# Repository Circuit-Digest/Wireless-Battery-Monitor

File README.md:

# Wireless-Battery-Monitor

<br>

Batteries are everywhere and can be found in many of the day-to-day life equipment. Most of them are powered by Li ion or LIfepo4 batteries nowadays. Even though they need much less maintenance when compared to traditional Lead acid batteries, it is essential to regularly monitor them to avoid damage or even accidents. That’s where BMS comes into play. They not only provide safety but also help extend battery life. But the problem with most common BMSs is that, if we want to manually check the battery health, we will have to physically access it. There are BMS’s that offer wireless monitoring functionality, but the issue is that they are pretty expensive. That’s why we have decided to design and build a DIY wireless battery monitoring system, which can be used with the existing BMS.
For this project we have chosen the AD7280 Lithium-Ion Battery Monitoring chip from Analog Devices, and for wireless connectivity we have chosen our favourite ESP32. The AD7280 is capable of monitoring up to 6S battery configuration. Here we have configured it to monitor 4S battery configuration since that’s the most commonly used battery system. The AD7280 offers a 12bit ADC with a conversion time of 1 us per channel. It also features cell balancing function, which can be controlled manually. The ESP32 is used for communication and to host a Async webserver which can be used to monitor the cell voltages and charge levels.

<br>
[Note: As this projects are very simple we are only providing the code, schemaitic, and a few essential images if you want to get the images or code explanations do check out the Circuit Digest website.
<br>
<br>

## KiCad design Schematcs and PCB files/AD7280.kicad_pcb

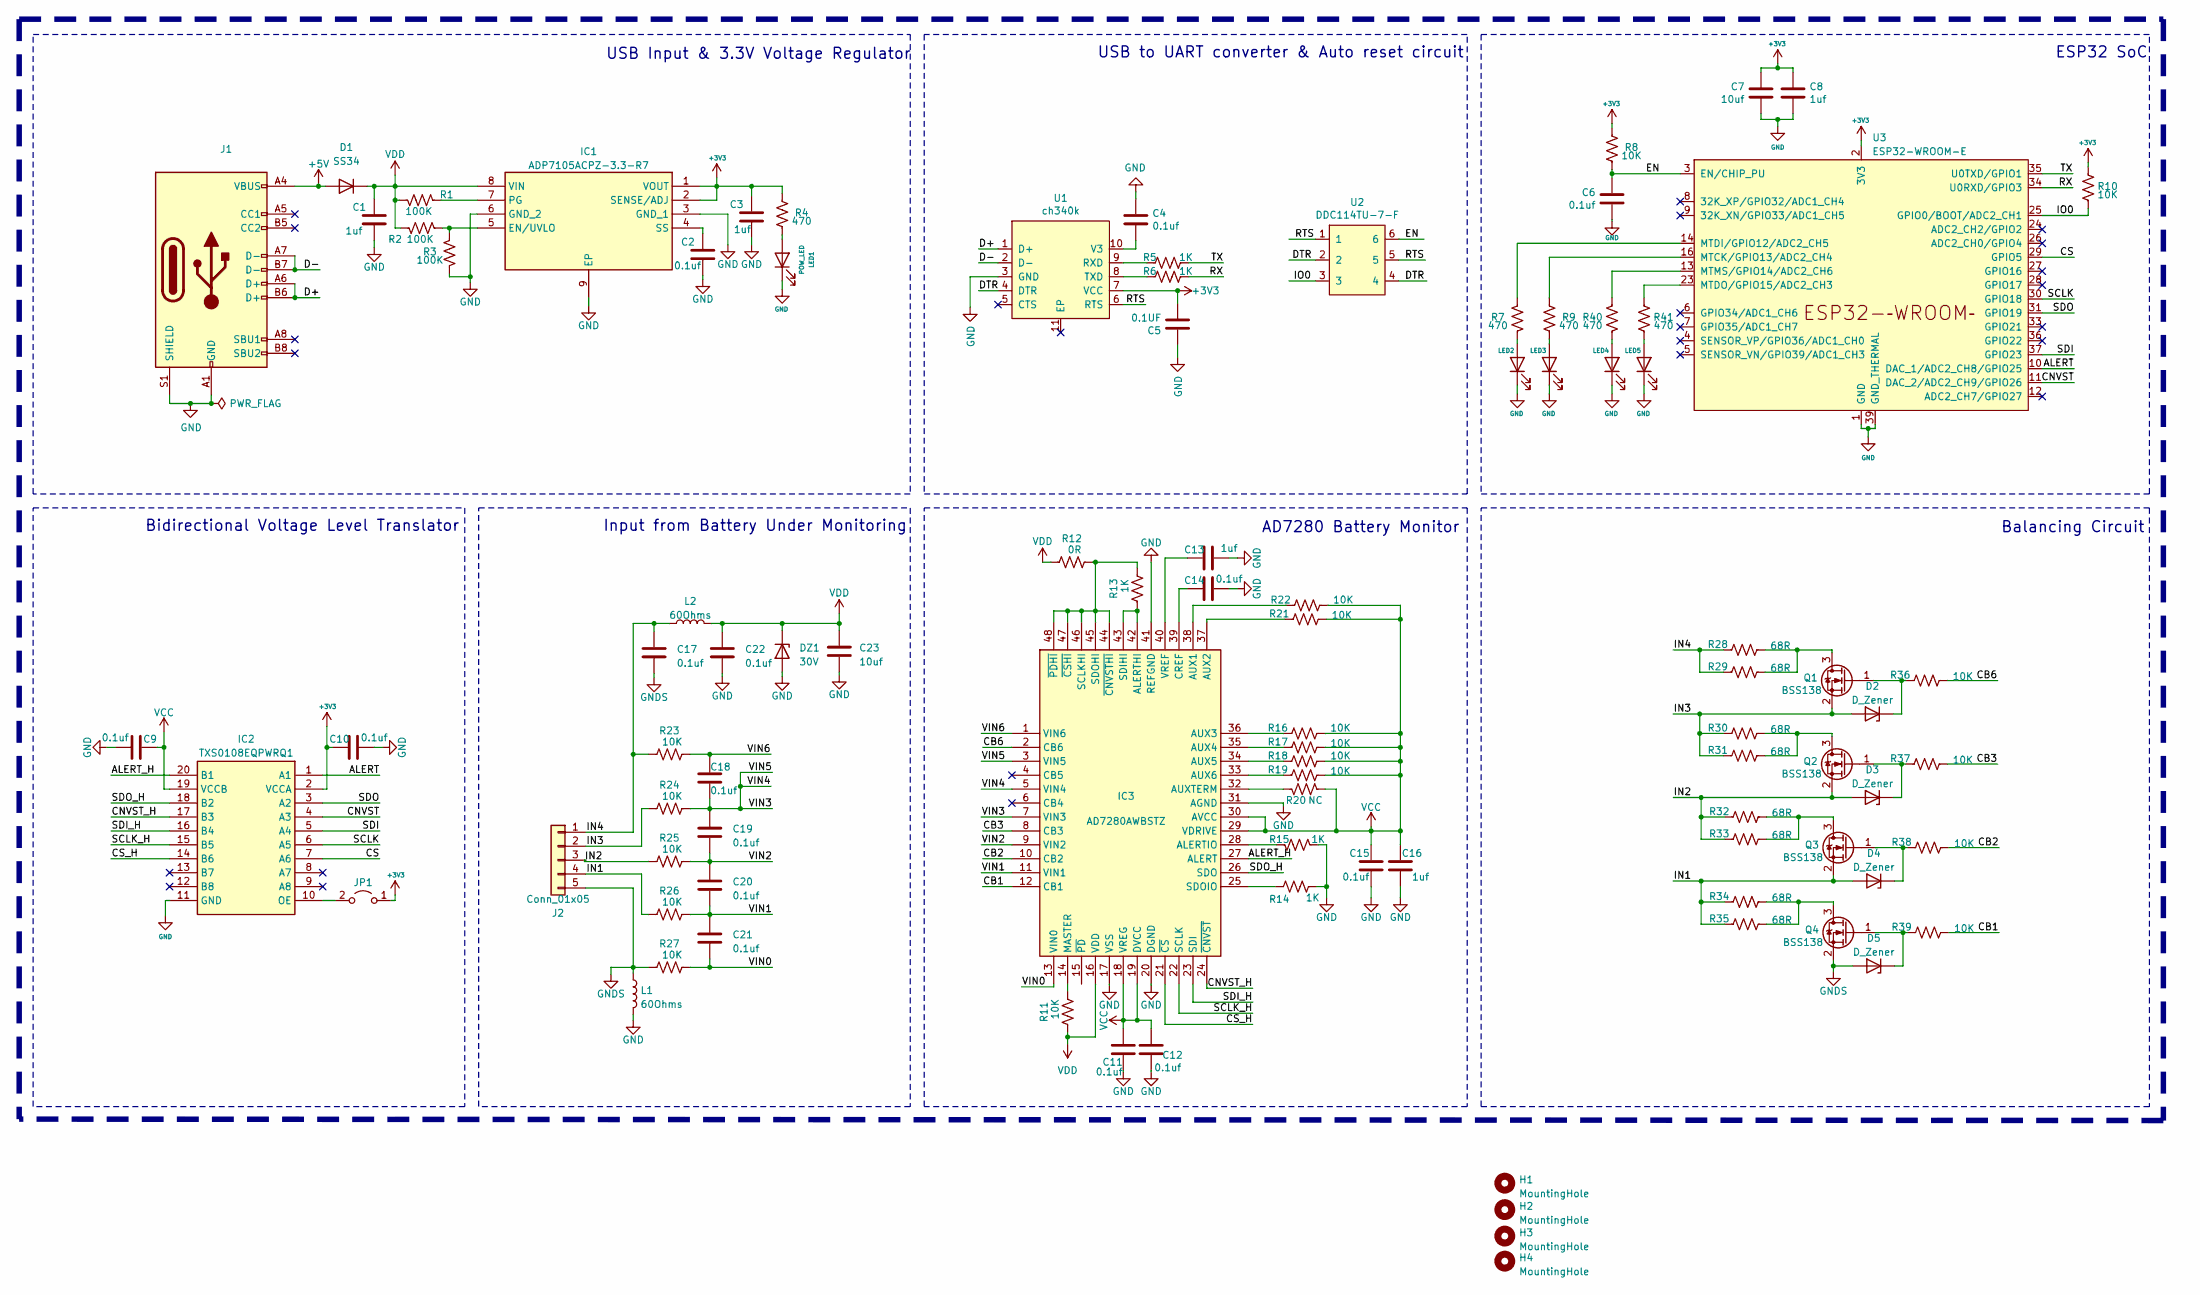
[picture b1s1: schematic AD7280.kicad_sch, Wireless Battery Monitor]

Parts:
C1: 1uf; L_0603_1608Metric
C2, C4, C6, C9, C10, C11, C12, C14, C15, C17, C18, C19, C20, C21, C22: 0.1uf; C_0603_1608Metric
C3, C8, C13, C16: 1uf; C_0603_1608Metric
C5: 0.1UF; C_0603_1608Metric
C7: 10uf; C_0805_2012Metric
C23: 10uf; C_1210_3225Metric
D1: SS34; D_SMA
D2, D3, D4, D5: D_Zener; D_SOD-123
DZ1: 30V; D_SMB
H1, H2, H3, H4: MountingHole; MountingHole_2.1mm
IC1: ADP7105ACPZ-3.3-R7; SON50P300X300X80-9N-D; Mouser Part Number 584-P7105ACPZ-3.3-R
IC2: TXS0108EQPWRQ1; SOP65P640X120-20N; Mouser Part Number 595-TXS0108EQPWRQ1
IC3: AD7280AWBSTZ; QFP50P900X900X160-48N; Mouser Part Number 584-AD7280AWBSTZ
J1: USB_C_Receptacle_USB2.0; USB_C_Receptacle_HRO_TYPE-C-31-M-12
J2: Conn_01x05; JST_XH_B5B-XH-A_1x05_P2.50mm_Vertical
JP1: Jumper_2_Open; SolderJumper-2_P1.3mm_Open_TrianglePad1.0x1.5mm
L1, L2: 60Ohms; L_1806_4516Metric; MFG Part number BLM41PG600SN1L
LED1, LED2, LED3, LED4, LED5: POW_LED; LED_0603_1608Metric
Q1, Q2, Q3, Q4: BSS138; SOT-23
R1, R2, R3: 100K; R_0603_1608Metric
R4, R7, R9, R40, R41: 470; R_0603_1608Metric
R5, R6, R13, R14, R15: 1K; R_0603_1608Metric
R8, R10, R11, R16, R17, R18, R19, R21, R22, R23, R24, R25, R26, R27, R36, R37, R38, R39: 10K; R_0603_1608Metric
R12: 0R; R_0603_1608Metric
R20: NC; R_0603_1608Metric
R28, R29, R30, R31, R32, R33, R34, R35: 68R; R_2512_6332Metric
U1: ch340k; ESSOP-10_3.9x4.9mm_P1.00mm
U2: DDC114TU-7-F; SOT-363_SC-70-6
U3: ESP32-WROOM-E; ESP32-WROOM-32E

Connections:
+3V3: C3.1, C5.2, C7.1, C8.1, C10.1, IC1.1 (VOUT), IC1.2 (SENSE/ADJ), IC2.2 (VCCA), JP1.1 (A), R4.2, R8.2, R10.2, U1.7 (VCC), U3.2 (3V3)
+5V: D1.2 (A), J1.A4 (VBUS), J1.A9 (VBUS), J1.B4 (VBUS), J1.B9 (VBUS)
/ALERT: IC2.1 (A1), U3.10 (DAC_1/ADC2_CH8/GPIO25)
/ALERT_H: IC2.20 (B1), IC3.27 (ALERT)
/CB1: IC3.12 (CB1), R39.2
/CB2: IC3.10 (CB2), R38.2
/CB3: IC3.8 (CB3), R37.2
/CB6: IC3.2 (CB6), R36.2
/CNVST: IC2.4 (A3), U3.11 (DAC_2/ADC2_CH9/GPIO26)
/CNVST_H: IC2.17 (B3), IC3.24 (~CNVST)
/CS: IC2.7 (A6), U3.29 (GPIO5)
/CS_H: IC2.14 (B6), IC3.21 (~CS)
/D+: J1.A6 (D+), J1.B6 (D+), U1.1 (D+)
/D-: J1.A7 (D-), J1.B7 (D-), U1.2 (D-)
/DTR: U1.4 (DTR), U2.2, U2.4
/EN: C6.1, R8.1, U2.6, U3.3 (EN/CHIP_PU)
/IN1: D4.2 (A), J2.4, Q3.2 (S), R26.1, R34.1, R35.1
/IN2: D3.2 (A), J2.3, Q2.2 (S), R25.1, R32.1, R33.1
/IN3: D2.2 (A), J2.2, Q1.2 (S), R24.1, R30.1, R31.1
/IN4: C17.1, J2.1, L2.1, R23.1, R28.1, R29.1
/IO0: R10.1, U2.3, U3.25 (GPIO0/BOOT/ADC2_CH1)
/RTS: U1.6 (RTS), U2.1, U2.5
/RX: R6.2, U3.34 (U0RXD/GPIO3)
/SCLK: IC2.6 (A5), U3.30 (GPIO18)
/SCLK_H: IC2.15 (B5), IC3.22 (SCLK)
/SDI: IC2.5 (A4), U3.37 (GPIO23)
/SDI_H: IC2.16 (B4), IC3.23 (SDI)
/SDO: IC2.3 (A2), U3.31 (GPIO19)
/SDO_H: IC2.18 (B2), IC3.26 (SDO)
/TX: R5.2, U3.35 (U0TXD/GPIO1)
/VIN0: C21.2, IC3.13 (VIN0), R27.2
/VIN1: C20.2, C21.1, IC3.11 (VIN1), R26.2
/VIN2: C19.2, C20.1, IC3.9 (VIN2), R25.2
/VIN3: C18.2, C19.1, IC3.3 (VIN5), IC3.5 (VIN4), IC3.7 (VIN3), R24.2
/VIN6: C18.1, IC3.1 (VIN6), R23.2
GND: C1.2, C2.2, C3.2, C4.1, C5.1, C6.2, C7.2, C8.2, C9.2, C10.2, C11.2, C12.2, C13.2, C14.2, C15.2, C16.2, C22.2, C23.2, DZ1.2 (A), IC1.3 (GND_1), IC1.6 (GND_2), IC1.9 (EP), IC2.11 (GND), IC3.17 (VSS), IC3.20 (DGND), IC3.31 (AGND), IC3.41 (REFGND), J1.A1 (GND), J1.A12 (GND), J1.B1 (GND), J1.B12 (GND), J1.S1 (SHIELD), L1.2, LED1.1 (K), LED2.1 (K), LED3.1 (K), LED4.1 (K), LED5.1 (K), R3.1, R14.1, R15.2, U1.3 (GND), U3.1 (GND), U3.15 (GND), U3.38 (GND), U3.39 (GND_THERMAL)
GNDS: C17.2, D5.2 (A), J2.5, L1.1, Q4.2 (S), R27.1
unnamed: D2.1 (K), Q1.1 (G), R36.1
unnamed: D3.1 (K), Q2.1 (G), R37.1
unnamed: D4.1 (K), Q3.1 (G), R38.1
unnamed: D5.1 (K), Q4.1 (G), R39.1
unnamed: IC1.5 (EN/UVLO), R2.1, R3.2
unnamed: IC1.7 (PG), R1.1
unnamed: C2.1, IC1.4 (SS)
unnamed: IC2.10 (OE), JP1.2 (B)
unnamed: IC3.42 (ALERTHI), IC3.43 (SDIHI), R13.1
unnamed: IC3.28 (ALERTIO), R15.1
unnamed: IC3.38 (AUX1), R22.1
unnamed: IC3.37 (AUX2), R21.1
unnamed: IC3.36 (AUX3), R16.1
unnamed: IC3.35 (AUX4), R17.1
unnamed: IC3.34 (AUX5), R18.1
unnamed: IC3.33 (AUX6), R19.1
unnamed: IC3.32 (AUXTERM), R20.1
unnamed: C14.1, IC3.39 (CREF)
unnamed: IC3.14 (MASTER), R11.2
unnamed: IC3.44 (~CNVSTHI), IC3.45 (SDOHI), IC3.46 (SCLKHI), IC3.47 (~CSHI), IC3.48 (~PDHI), R12.2, R13.2
unnamed: IC3.25 (SDOIO), R14.2
unnamed: C13.1, IC3.40 (VREF)
unnamed: LED1.2 (A), R4.1
unnamed: LED2.2 (A), R7.1
unnamed: LED3.2 (A), R9.1
unnamed: LED4.2 (A), R40.1
unnamed: LED5.2 (A), R41.1
unnamed: Q1.3 (D), R28.2, R29.2
unnamed: Q2.3 (D), R30.2, R31.2
unnamed: Q3.3 (D), R32.2, R33.2
unnamed: Q4.3 (D), R34.2, R35.2
unnamed: R5.1, U1.9 (RXD)
unnamed: R6.1, U1.8 (TXD)
unnamed: C4.2, U1.10 (V3)
unnamed: R9.2, U3.16 (MTCK/GPIO13/ADC2_CH4)
unnamed: R7.2, U3.14 (MTDI/GPIO12/ADC2_CH5)
unnamed: R41.2, U3.23 (MTDO/GPIO15/ADC2_CH3)
unnamed: R40.2, U3.13 (MTMS/GPIO14/ADC2_CH6)
VCC: C9.1, C11.1, C12.1, C15.1, C16.1, IC2.19 (VCCB), IC3.18 (VREG), IC3.19 (DVCC), IC3.29 (VDRIVE), IC3.30 (AVCC), R16.2, R17.2, R18.2, R19.2, R20.2, R21.2, R22.2
VDD: C1.1, C22.1, C23.1, D1.1 (K), DZ1.1 (K), IC1.8 (VIN), IC3.16 (VDD), L2.2, R1.2, R2.2, R11.1, R12.1

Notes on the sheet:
Balancing Circuit
Input from Battery Under Monitoring
ESP32 SoC
Bidirectional Voltage Level Translator
USB to UART converter & Auto reset circuit
USB Input & 3.3V Voltage Regulator
AD7280 Battery Monitor

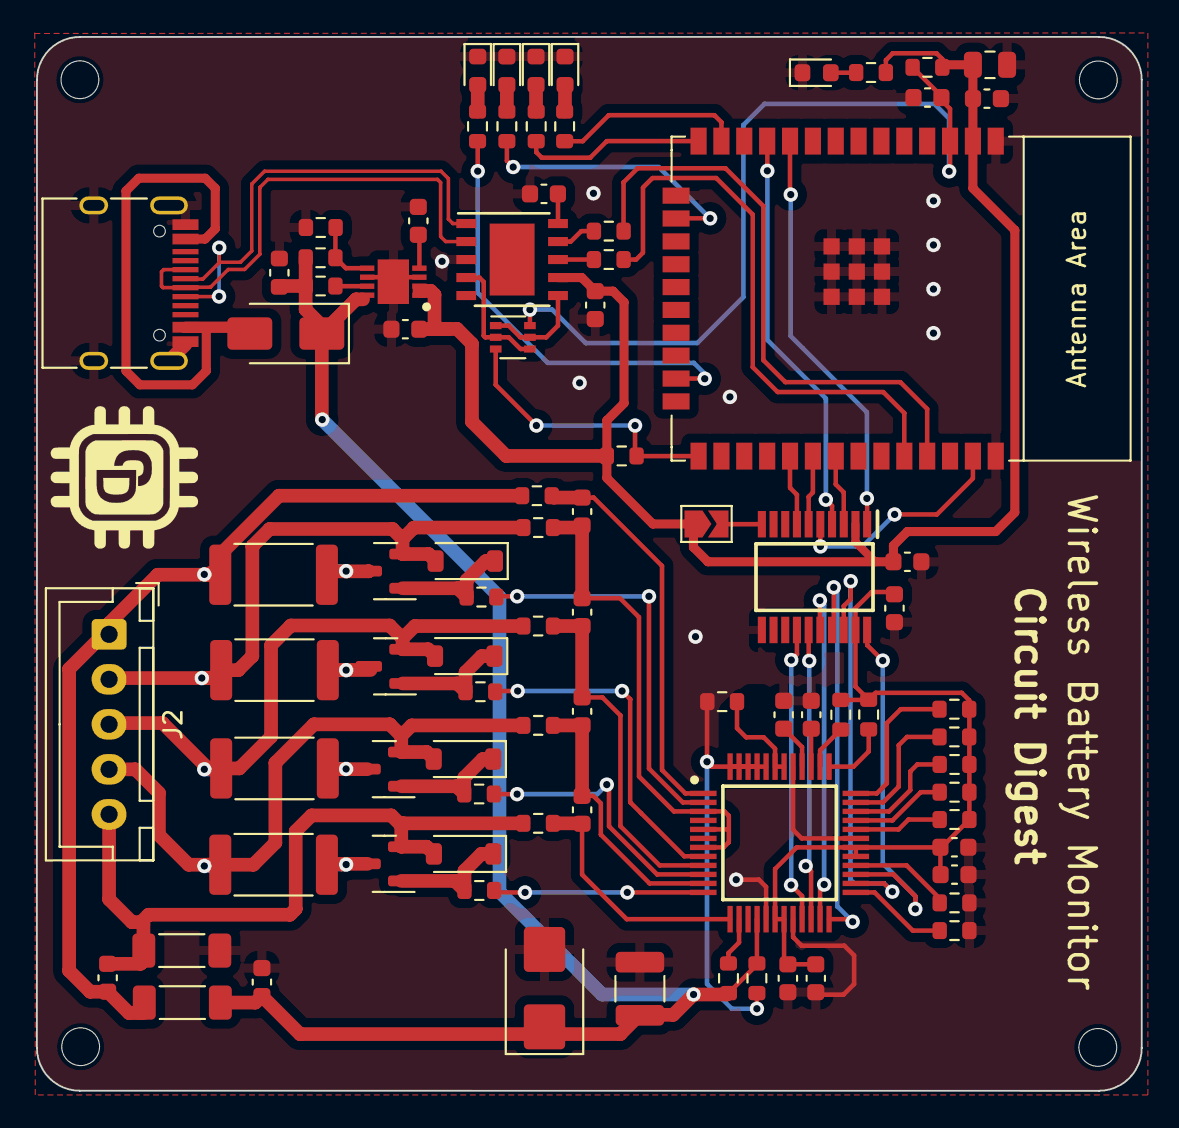
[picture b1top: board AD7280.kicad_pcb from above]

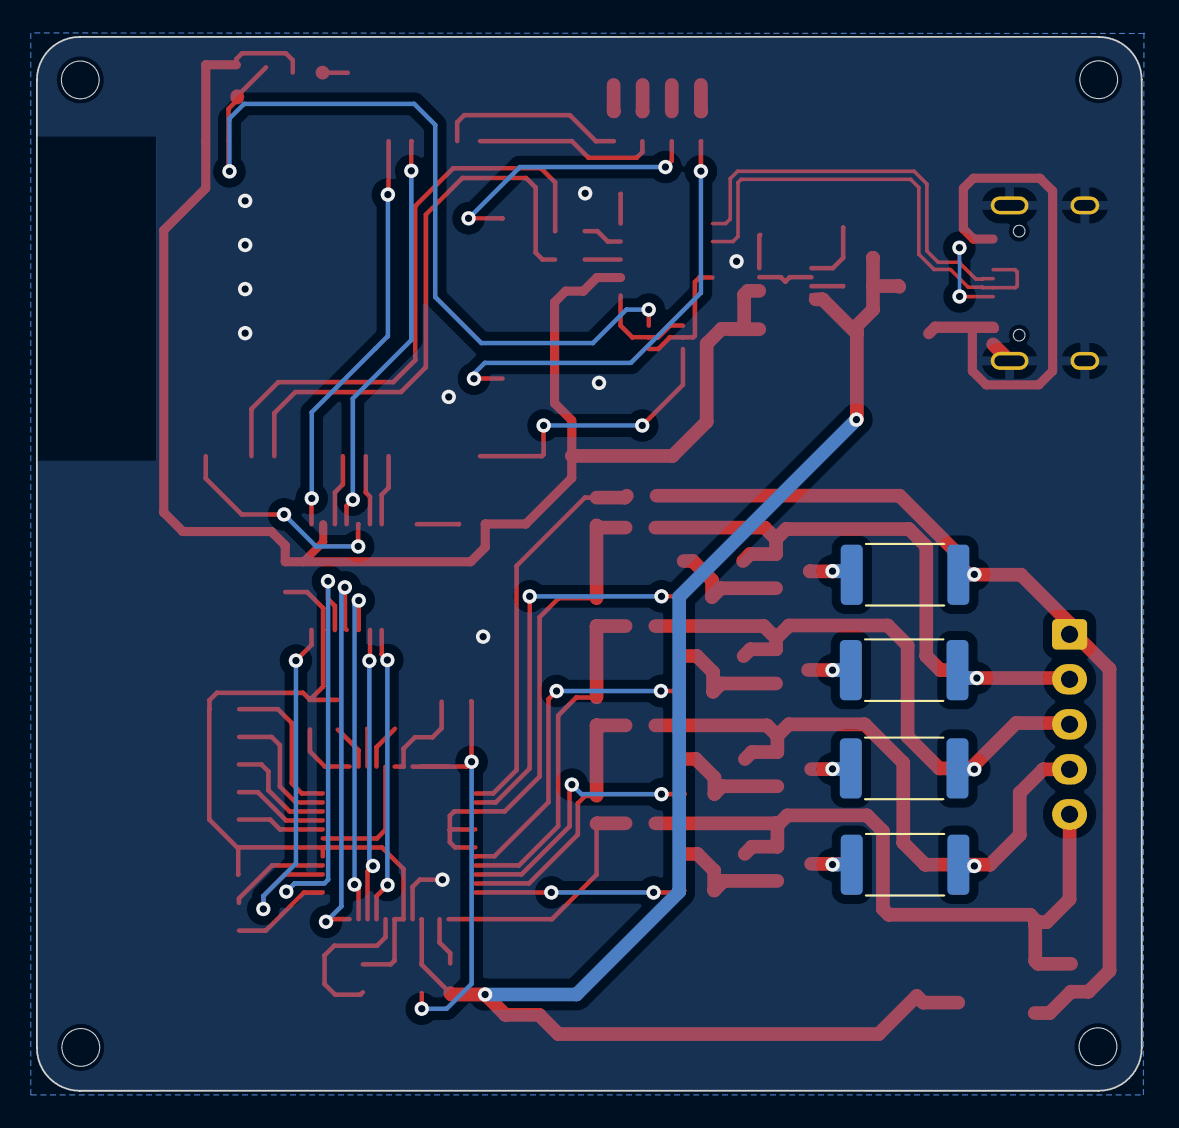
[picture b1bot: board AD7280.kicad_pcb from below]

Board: 2 copper layers, 61.4 x 58.6 mm, 94 parts (4 on the bottom side), 77 nets.

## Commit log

2023-11-21 Update Code.ino ad option to ignore values with CRC error
